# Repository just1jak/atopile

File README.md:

# Atopile Local 0.4.1 source checkpoint

**Moving to another computer? Start with [CONTINUE-HERE.md](CONTINUE-HERE.md).**
It covers this source checkpoint and the unfinished integrated-SD scanner PCB.

A local VS Code continuation of atopile 0.15.9 with native KiCad schematic
export, ChatGPT through Codex or your own AI provider, local component imports,
and net/placement/DRC tools. This is an independent
fork, not an official atopile release.

This checkpoint preserves the 0.4.1 source and subsequent local KiCad 10
editing, Codex tool-catalog, and startup fixes. The installed extension on the
original Mac reports 0.4.1; this newer source checkpoint has not been packaged
as a new release. Its focused backend checks passed **114 tests**. See
[extension-handoff.md](extension-handoff.md) for exact recovery and rebuild steps.

## Start on this Mac

On this Mac, double-click **Open Atopile Local.command** beside the source
folder. It opens the included circuit in VS Code. Select the build target and
choose **Inspect → Schematic**. Other inspection views remain available beside it.

For this checkpoint, rebuild and install from the checked-out source using the
steps in `extension-handoff.md`. An older downloaded release archive installs
that release's source rather than these later changes. The installer registers
the runtime for other VS Code workspaces too. ChatGPT (Codex) is the default AI provider.
Run **Atopile Local: Connect ChatGPT** to reuse your local Codex sign-in or start
Codex's browser sign-in. No separate API key is needed. Your ChatGPT plan's
Codex usage limits apply; this does not grant unlimited usage or add credits.

The connection uses the official local `codex app-server` interface. Codex owns
sign-in, credential storage, and renewal. Atopile Local does not copy account
tokens into its settings or webviews. It requires ChatGPT authentication and
will not silently switch to API billing. The compiler and circuit tools still
run locally; prompts and tool results go to OpenAI for AI assistance.

Use **Atopile Local: Configure AI Provider** to select a separate OpenAI-compatible
or Anthropic provider instead, then **Atopile Local: Set AI API Key** to store that
provider's key in VS Code. Optional `atopileLocal.agent.codexPath` selects a Codex
executable; leave it blank for automatic discovery. A blank model uses Codex's
default model when ChatGPT is selected.

The compiler, parts, and viewers work without AI. API providers require their
own key; a loopback model server may omit a key. OpenAI-compatible
endpoints must implement the Responses API, streaming, and tool calls. Datasheet
file search also requires Files/Vector Stores support. A Chat Completions-only
server is not supported by this release. Leave the endpoint blank for the
selected provider's default; custom Anthropic endpoints use the API origin
rather than an OpenAI-style `/v1` suffix. Your provider's prices/limits apply.

## Portable setup

Requires VS Code 1.105+, uv, and KiCad for native schematic export, layout and DRC. ChatGPT assistance
also requires a Codex CLI with app-server dynamic tools and a ChatGPT plan that
includes Codex access. Tested on Apple
Silicon macOS with Python 3.14.6 and KiCad 10.0.7. The `.command` launcher is
for macOS; Linux can use `python3 local/launch.py`. Windows launcher packaging
is not included.

Keep the engine outside iCloud, OneDrive, and other folders that automatically
offload files. The current fork includes a verified installer that puts it in
local application storage (on macOS, `~/Library/Application Support/Atopile Local`).
Download the release source ZIP, `SHA256SUMS.txt`, and VSIX, then run this from
the fork checkout:

```sh
python3 local/install_local_runtime.py \
  --archive /path/to/atopile-local-source.zip \
  --checksum-file /path/to/SHA256SUMS.txt
python3 local/launch.py
```

Download the source and extension from the
[GitHub release](https://github.com/just1jak/atopile/releases/tag/local-v0.4.0),
or clone the fork's `feature/atopile-local` branch for the installer. Before
launching, install the VSIX using VS Code's **Extensions: Install from VSIX**
command. The installer verifies the archive, installs pinned dependencies,
and checks startup before changing VS Code's runtime location. Failed setup
keeps the previous location; retrying the same archive resumes setup.
To open another existing project, use `python3 local/launch.py /path/to/project`.

```sh
git clone --branch feature/atopile-local https://github.com/just1jak/atopile.git
cd atopile
```

For this source checkpoint, use a fully local checkout, run
`python3 local/setup_runtime.py`, rebuild with `python3 local/build_extension.py`,
then install using `python3 local/install_extension.py`. Do not use `--download`
when you intend to run the checkpoint source and its rebuilt UI.

The native compiler is the pinned atopile 0.15.9 wheel. Modified Python source
runs over that wheel, avoiding a local Zig rebuild. The wrapper uses safe
Python import precedence and stores fork state in `.state/`; it disables atopile
telemetry and migration-notice requests. The runtime handoff goes in this fork's
own VS Code global storage and does not alter official atopile settings.

## Local design workflow

```sh
bin/ato-local build examples/offline-indicator --target default
bin/ato-local create part-from-kicad --help
bin/ato-local create part-from-pinout --help
```

Open the **Atopile Local** activity-bar view to build, browse components and
nets, inspect pinouts, and open the PCB/3D viewers. The independent agent can
edit project files, build and debug circuits, read logical nets, inspect or
change placements (with backups), add or delete copper, and run KiCad DRC.

## Board access in chat

The chat identifies itself as **Atopile Local** and shows its configured AI
provider. Before each message, the host checks the session's selected PCB with
the local inspection tool. **Board last read** reports the checked target,
part count, and net count. A failed check shows the actual error.

The agent can read placement and logical nets, move or rotate unlocked
components, add straight track segments and through-vias, delete copper by
UUID, and run KiCad DRC. Placement changes preserve existing tracks but do not
reroute them. Copper tools require explicit net, canonical copper layer, and
geometry; creating a segment does not prove its clearance or complete routing.
Ask it to inspect the board first, state any fixed connector positions and
board dimensions, and review native DRC after edits.

KiCad 10 edits preserve unsupported source fields and unrelated native locks.
Locked targets and `FBRK:notouch` geometry are protected. The scoped editor
supports placement and copper changes; settings, net membership, zone changes,
new footprints, and complex flips remain native KiCad work. Stale external
changes are rejected instead of overwritten, and successful edits create
backups. Save edits in KiCad before switching editors.

Version 0.3.1 fixes Codex tool discovery for the full production tool catalog.
After updating, reload the VS Code window so the backend and tool bridge restart.
Existing chat history is retained.

## Schematics in KiCad

After building, open **Inspect → Schematic** and choose **Open in KiCad**.
If the project has a native schematic, explicitly map it to the build target
in `.atopile-local.json`:

```json
{"schematics": {"v240": "elec/schematic/ChryslerScanner_V240.kicad_sch"}}
```

Normal opening preserves that file and all child sheets. Paths must remain
inside the selected project; the hierarchy is validated before native KiCad
reads it. The app does not guess which existing schematic belongs to a target.

For projects without a mapping, Atopile Local saves a real `.kicad_sch` file, with embedded KiCad symbols and
nets taken from the PCB's actual pad assignments, then opens KiCad's Schematic
Editor. KiCad must be installed: each new snapshot is checked using its native
netlist exporter. The saved file remains available if the editor cannot launch.

The panel shows the saved file's location. Reopening the same circuit revision
uses the saved file, preserving edits made in KiCad. **Generate new from circuit**
creates a separate snapshot and opens it; it never overwrites an earlier file.
Exports live under the selected target's build output in a `schematic` folder.
Keep a copy outside `build/` before cleaning build artifacts.

This is a code-to-schematic export: edits in KiCad do not update `.ato` source.
The existing PCB is left in place. Source and PCB footprint identifiers are
included as symbol properties, but native KiCad PCB cross-probing/relinking is
not established by this export. Missing symbols, unsupported multi-unit parts,
and ambiguous pin mappings stop export with a specific error. This initial
exporter supports up to 256 components per snapshot.

**Preview connections** opens the optional inline preview with net highlighting
and links to source declarations and the PCB view. Its wiring describes logical
connections rather than physical PCB trace routes. Power/data Trees remain
separate views and may be empty for generic parts.

The routed offline indicator has three local components, three nets, and a
32 x 18 mm outline. Its layout is a specific hand-authored recipe. Generic
local parts are included in the JSON BOM; unsourced parts are excluded from the
JLCPCB assembly CSV. See `examples/offline-indicator/README.md`.

## Service boundaries

Local builds with locally imported parts do not need atopile sign-in. Automatic
online component selection still uses atopile's service and requires sign-in.
DeepPCB automatic placement/routing remains hosted and is labeled in the UI;
no general local autorouter is included. Web search uses your own `EXA_API_KEY`.
Manual local layout and local agent placement/DRC do not use those services.
The KiCad 10 source-preserving adapter retains native locks and rejects edits
to locked targets. Unsupported changes stop with an error rather than dropping
unknown native fields.

## Rebuild and verify

```sh
python3 local/build_extension.py
PYTHONPATH=$PWD/src ATOPILE_LOCAL_DATA_DIR=$PWD/.state FBRK_TELEMETRY=0 \
  .venv/bin/python -m pytest test/agent test/libs/test_kicad_part_import.py \
  test/exporters/pcb/kicad/test_pcb_transformer.py -q
.venv/bin/python local/verify_backend.py
python3 local/verify_offline.py
```

The recovered checkpoint passed 114 focused backend tests, including native
KiCad edit/connectivity checks and mocked Codex protocol checks, on 2026-10-20.
The full frontend dependency install, TypeScript checks, and VSIX rebuild were
not repeated for this checkpoint. See `extension-handoff.md` for the exact test
command and the distinction from older release verification.

The earlier verification record is `local/VERIFICATION.json`; demo connectivity and DRC
reports are under `examples/offline-indicator/`. No physical hardware test was
performed. Passing DRC does not verify electrical behavior or supplier suitability.

## Source and licenses

Based on the public PyPI atopile 0.15.9 source distribution, SHA-256
`681cc1e123646dd133de31b631aedaf4eaac88682613b4f82d1da4b3ef8b4e8e`.
Upstream MIT notices are retained; local import work retains the Axiovel MIT
attribution in `local/IMPORTER_ATTRIBUTION.md`. Bundled 3D decoders include their
Apache-2.0 notices and Three.js MIT license. The original README is preserved
at `local/UPSTREAM_README.md`. The three standard KiCad demo symbols retain
their CC-BY-SA 4.0 library license and exception in
`examples/offline-indicator/assets/KICAD-SYMBOLS-LICENSE.md`.

Codex-managed ChatGPT authentication is documented for local/open-source apps.
This integration is for local use; a hosted or commercial service needs its own
supported sign-in integration. See [OpenAI's app-server documentation](https://learn.chatgpt.com/docs/app-server).

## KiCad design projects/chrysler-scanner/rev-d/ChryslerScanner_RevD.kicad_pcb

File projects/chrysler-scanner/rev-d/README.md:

# Rev D switchable legacy and CAN diagnostics

Open [ChryslerScanner_RevD.kicad_pro](ChryslerScanner_RevD.kicad_pro) in KiCad
10. Sheet 25 is the CAN transceiver, sheet 26 switches OBD pins 6 and 14
between CAN and the retained legacy branches, and sheet 27 gates CAN TX.
Sheet 28 adds series isolation and a hardware transmit timer. This is a
development revision. Use the board and schematic from the same revision.

## Mode control

U26 is an MCP23008 on the existing I2C bus at seven-bit address 0x20. GP0
requests CAN and GP1 requests Legacy. Both request lines have pull-downs.
U27 decodes the requests in hardware and its enable is driven by N_R88_2,
the existing supervised expander reset/permit. That net also resets U26
and cuts the coil return through Q27. Only the normally open contacts of
K1 and K2 are wired to the bus branches. K3 is in series with K1 and K4
is in series with K2. K3 and K4 have separate coil sinks driven by the
raw decoder outputs and the hardware permit. The primary relays use
delayed decoder outputs. A closed contact or a stuck-on coil driver in
one relay leaves the other contact in series on each conductor able to
isolate the unselected branch.

| Hardware permit | Request GP1:GP0 | OBD pins 6 and 14 |
| --- | --- | --- |
| Low | Any | Both branches open after relay release |
| High | 00 | Both branches open |
| High | 01 | CAN branch only |
| High | 10 | Legacy branch only |
| High | 11 | Both branches open |

The 110 × 96 mm PCB extends the lower edge by 41 mm from Rev C to make
room for the selector, series relays and TX interlock. It retains the
four Rev C mounting-hole centers.
Confirm the revised outline and enclosure fit before releasing fabrication.

Each relay has a delayed pickup and quicker turnoff path from the decoder
through its RC network and Schmitt buffer. The firmware must write 00
between modes and wait through the qualified contact release, bounce and
discharge interval before requesting the other mode. Firmware startup
must clear the output latch before configuring the request GPIOs as outputs.
Drop the hardware permit if expander setup, readback or a mode transition
fails. CCD, PCI and SCI receive on pins 7/15 retain their existing wiring.

CAN RXD feeds GPIO39. STB defaults high and is pulled low for CAN capture.
D40 protects the CAN branch. The selector restores physical access to the
legacy branches. Existing firmware continues to inhibit VBB/VPP and active
transmission. A future programming release requires independent isolation
and contact-state safeguards. A coil command or expander readback cannot
prove that a contact opened.

## Active diagnostics and passive default

U26 GP2 is the TX arm request and defaults low through R146. U29 through
U31 require the hardware permit, the raw CAN decode, the delayed CAN relay
command, a low Legacy relay command and the explicit arm. U32 is a buffer
with a high impedance output when the permit is low. R149 then holds the
transceiver TXD high, which is the recessive state. The raw decode disables
TX when leaving CAN even if the delayed CAN relay signal is still high.
U33 is a rising-edge, nonretriggerable LTC6993-1 with a nominal 1.028 s
window. U34 requires both the window and the original arm. Dropping the
arm cancels TX immediately, and an arm held high cannot extend the pulse.
The firmware's 900 ms window still governs normal requests. A later arm
edge can start another hardware window after the one-shot has rearmed.
On reset, the selector opens both branches. Selecting CAN with GP2 low
gives the passive capture mode and permits TWAI to run in listen-only mode.

U10 GPIO2, pad 22, is the Rev D TWAI TX candidate and connects only to the
buffer input and a 47 kΩ pull-down. This keeps the required low strap for
joint download mode. Verify cold boot and USB download across supplies and
temperatures. Firmware must establish recessive TX before asserting GP2.

Build the firmware with `pio run -e rev_d_can` from the firmware directory.
Use the USB CLI on a terminated bench bus once the board is qualified.

```powershell
python tools/scanner.py can-mode passive --port COM7 --bitrate 500000
python tools/scanner.py can-read pid --port COM7 --pid 0x0c
python tools/scanner.py can-read dtc --port COM7
python tools/scanner.py can-read vin --port COM7
python tools/scanner.py can-mode legacy --port COM7
python tools/scanner.py can-mode open --port COM7
```

The selector starts open. Selecting CAN starts TWAI in listen-only mode.
An explicit USB lease and request are required to arm TX. The diagnostic
window has a 900 ms software budget and returns to listen-only after a reply
or timeout. A controller or ISO-TP fault drops the arm and opens the selector.
The CH340 provides no physical USB disconnect signal to the MCU.
Active mode can send requests, ISO-TP flow control, ACKs, and error frames.
The implementation supports 250/500 kbit/s Classical CAN with standard IDs,
functional read-only OBD requests, and one ISO-TP responder per request.
Desktop and mobile diagnostic controls are outside this firmware target.
Relay timing and isolation still require physical verification.

## Checks and bring-up

KiCad 10 full DRC reports zero violations, unconnected items or schematic
parity issues. The pad connectivity audit finds all 246 ground pads in one
group. The MCU fanout uses a local CAN RX escape on L2. Keep the
filled-and-capped processing specified in the board for vias whose drills
intersect SMD lands.

KiCad 10 all-severity ERC passed with zero violations. The netlist checker
compares every net to Rev C plus the declared changes and evaluates all eight
steady-state permit/request combinations using the normally open relay contacts.
The TX logic check covers 128 combinations of route request, hardware
permit, relay commands, TX arm and the timer output. Only the fully
enabled CAN state allows TX. The contact model
forces each relay closed in turn and checks isolation on both conductors.
It covers one stuck relay or driver. The decoder, supply and supervisor
remain common to the drive paths. Bench checks cover physical timing
and leakage.

```powershell
kicad-cli sch erc --severity-all --exit-code-violations ChryslerScanner_RevD.kicad_sch
kicad-cli sch export netlist --format kicadxml -o rev-d-netlist.xml ChryslerScanner_RevD.kicad_sch
python check_netlist.py rev-d-netlist.xml
kicad-cli pcb drc --all-track-errors --schematic-parity --severity-all --refill-zones --exit-code-violations ChryslerScanner_RevD.kicad_pcb
```

Before fabrication release, verify mechanical land patterns and the relay supply
and permit loading. Measure the minimum pickup delay and maximum release and
bounce including diode flyback, tolerance, temperature, supply sequencing
and rapid changes. Check both poles during MCU reset, missing heartbeat,
brownout and recovery. Short one normally open contact or force one coil
driver on at a time and verify that the other series contact isolates the
unselected branch. Qualify these cases
before connecting a vehicle or permitting programming voltages. Confirm
CAN signal quality and listen-only capture on a terminated bench bus
with separate transmitting and acknowledging nodes.

Exercise PID, DTC and multi-frame VIN responses on the bench at both bit
rates. Scope TXD and both relay outputs during the request, response, timeout
and bus-off cases. Confirm passive capture contributes no ACK, verify
transmit permit removal on lease release, and measure the time to recessive
TXD after a watchdog fault. With CAN selected and the heartbeat running,
hold the arm high through expiry and scope the timer output, buffer enable
and TXD. Repeat with an arm drop during the pulse and with trigger edges
during the pulse to verify immediate cancel and no pulse extension.

[Relay datasheet](https://components.omron.com/sites/default/files/datasheet_pdf/K106-E1.pdf)
· [I2C expander datasheet](https://ww1.microchip.com/downloads/en/DeviceDoc/MCP23008-MCP23S08-Data-Sheet-20001919F.pdf)
· [CAN transceiver datasheet](https://www.ti.com/lit/ds/symlink/tcan1042h-q1.pdf)

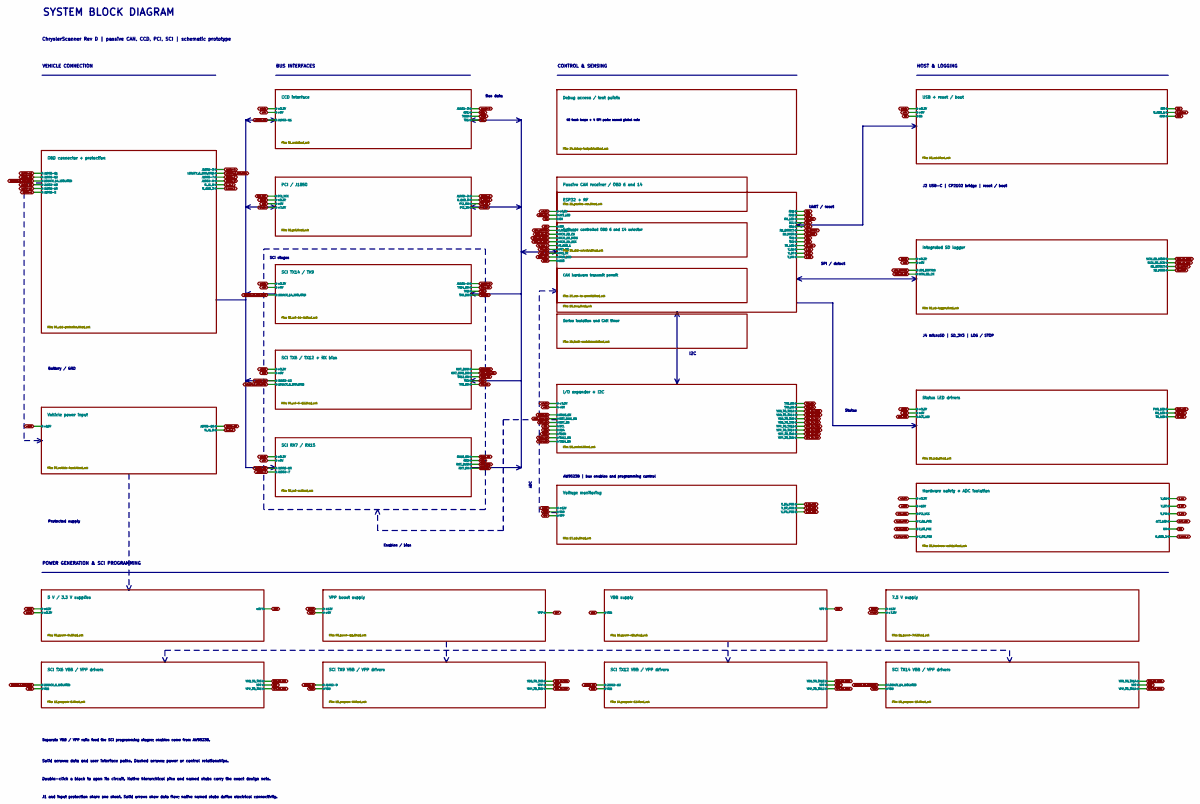
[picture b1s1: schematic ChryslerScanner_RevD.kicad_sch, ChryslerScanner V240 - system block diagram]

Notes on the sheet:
SYSTEM BLOCK DIAGRAM
ChryslerScanner Rev D | passive CAN, CCD, PCI, SCI | schematic prototype
VEHICLE CONNECTION
BUS INTERFACES
CONTROL & SENSING
HOST & LOGGING
SCI stages
Bus data
UART / reset
SPI / detect
Status
I2C
ADC
Enables / bias
Battery / GND
Protected supply
POWER GENERATION & SCI PROGRAMMING
Separate VBB / VPP rails feed the SCI programming stages; enables come from AW9523B.
J2 USB-C | CP2102 bridge | reset / boot
J4 microSD | SD_3V3 | LOG / STOP
AW9523B | bus enables and programming control
Solid arrows: data and user interface paths. Dashed arrows: power or control relationships.
Double-click a block to open its circuit. Native hierarchical pins and named stubs carry the exact design nets.
J1 and input protection share one sheet. Solid arrows show data flow; native named stubs define electrical connectivity.
48 hook loops + 4 SPI pads; named global nets

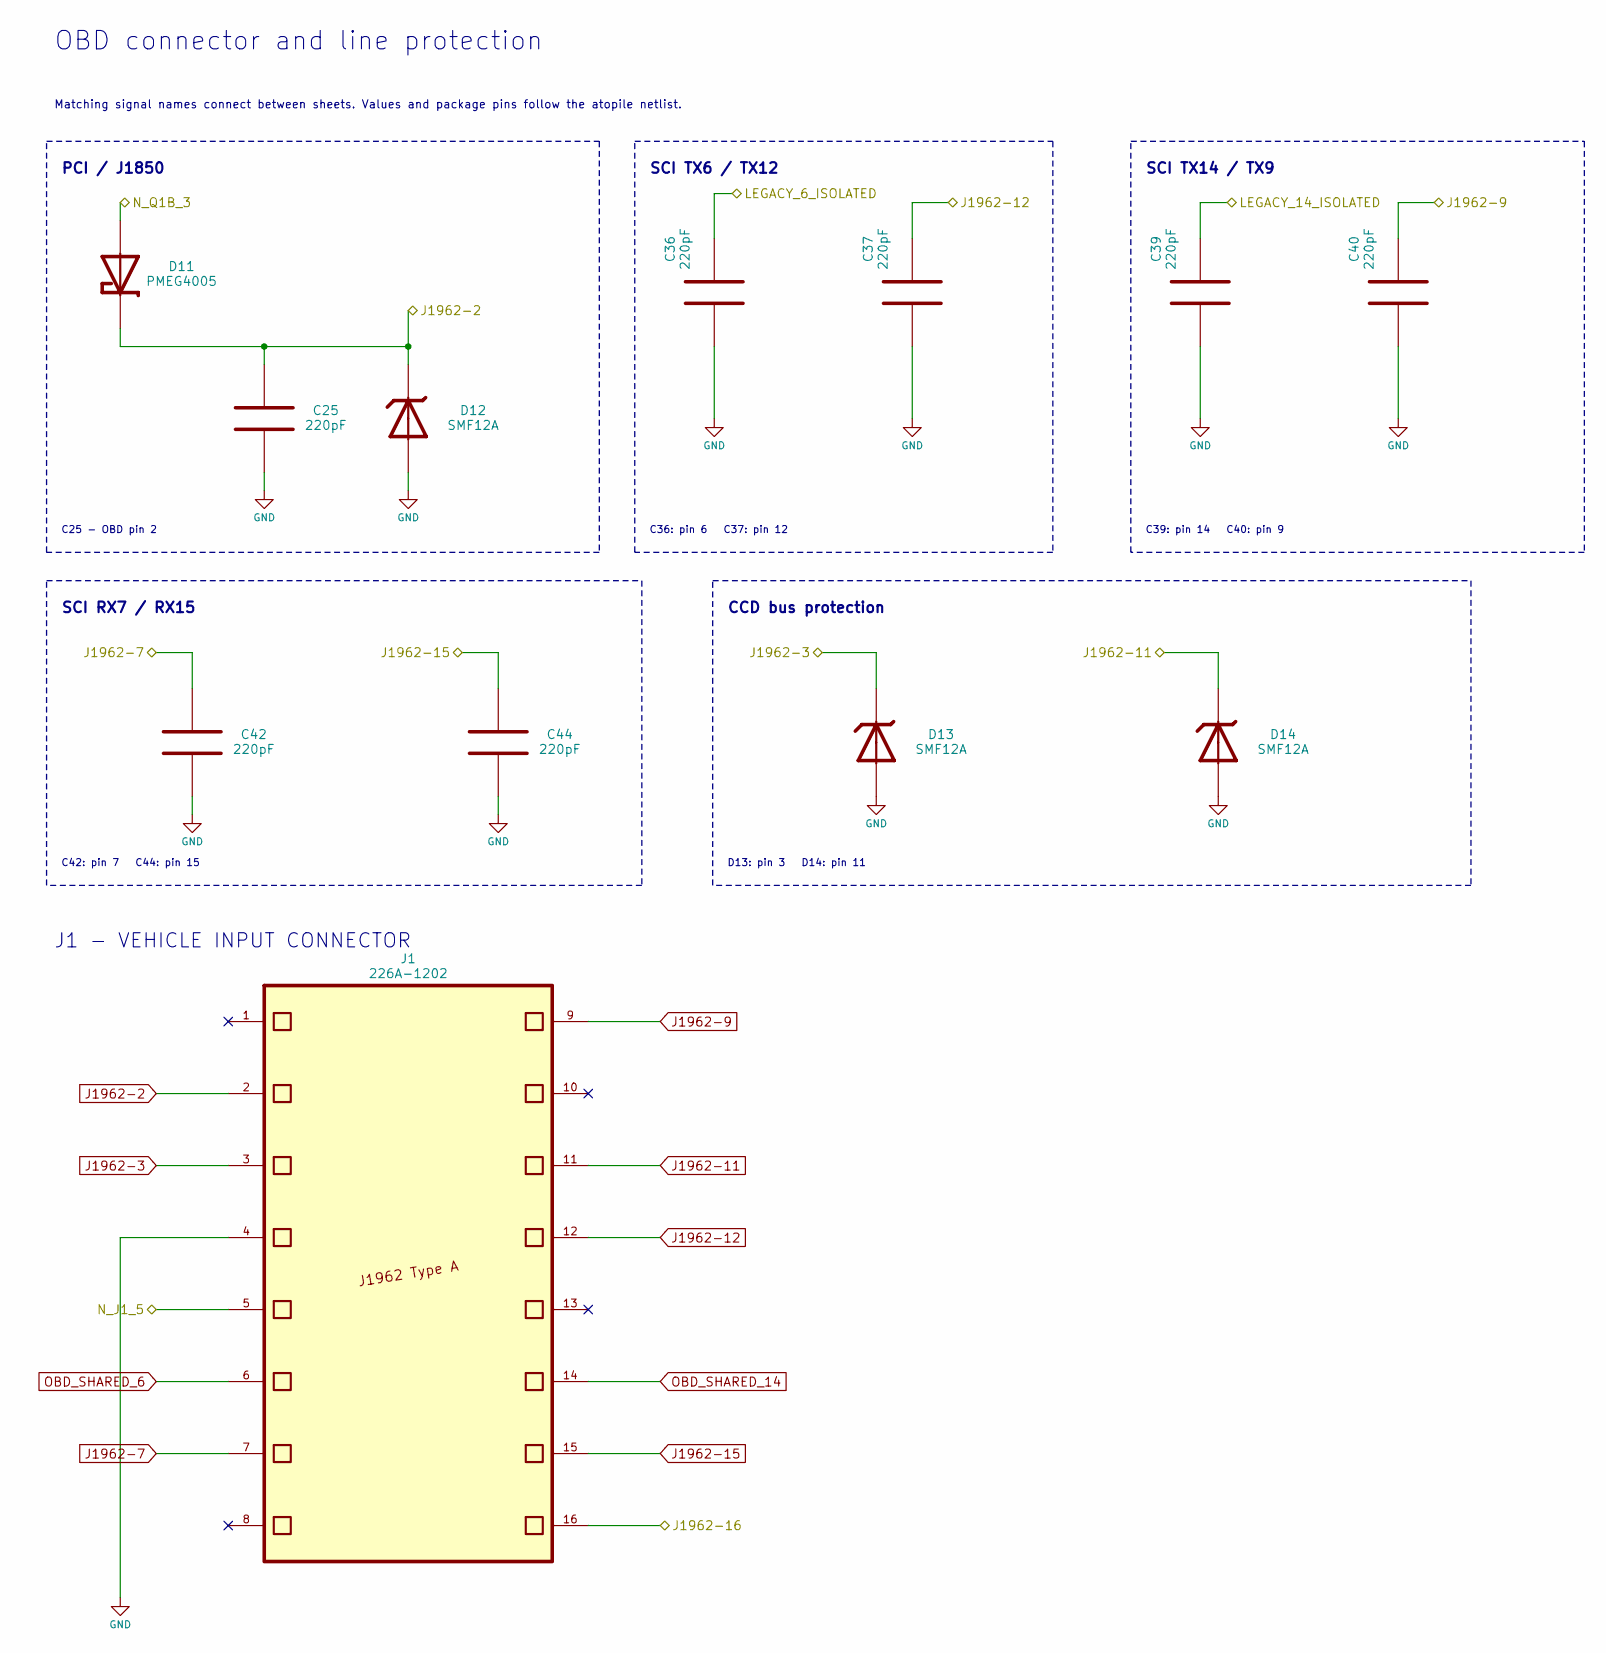
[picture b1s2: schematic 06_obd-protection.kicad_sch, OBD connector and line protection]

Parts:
C25, C36, C37, C39, C40, C42, C44: 220pF; C_0603_1608Metric; Selected Voltage Rating 100V; Tolerance 5%; MPN C0603C221J1GACTU
D11: PMEG4005; D_SOD-123; MPN PMEG4005EGWX
D12, D13, D14: SMF12A; D_SOD-123; MPN SMF12A
J1: 226A-1202; OBDII_ATTEND_226A-1202; MPN 226A-1202

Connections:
GND: C25.2, C36.1, C37.1, C39.1, C40.1, C42.2, C44.2, D12.2, D13.2, D14.2, J1.4; also elsewhere on the board
J1962-2: C25.1, D11.1, D12.1, J1.2; also elsewhere on the board
J1962-3: D13.1, J1.3; also elsewhere on the board
J1962-7: C42.1, J1.7; also elsewhere on the board
J1962-9: C40.2, J1.9; also elsewhere on the board
J1962-11: D14.1, J1.11; also elsewhere on the board
J1962-12: C37.2, J1.12; also elsewhere on the board
J1962-15: C44.1, J1.15; also elsewhere on the board
J1962-16: J1.16; also elsewhere on the board
LEGACY_6_ISOLATED: C36.2; also elsewhere on the board
LEGACY_14_ISOLATED: C39.2; also elsewhere on the board
N_J1_5: J1.5; also elsewhere on the board
N_Q1B_3: D11.2; also elsewhere on the board
OBD_SHARED_6: J1.6; also elsewhere on the board
OBD_SHARED_14: J1.14; also elsewhere on the board

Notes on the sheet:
J1 - VEHICLE INPUT CONNECTOR
Matching signal names connect between sheets. Values and package pins follow the atopile netlist.
OBD connector and line protection
PCI / J1850
C25 - OBD pin 2
SCI TX6 / TX12
C36: pin 6 C37: pin 12
SCI TX14 / TX9
C39: pin 14 C40: pin 9
SCI RX7 / RX15
C42: pin 7 C44: pin 15
CCD bus protection
D13: pin 3 D14: pin 11

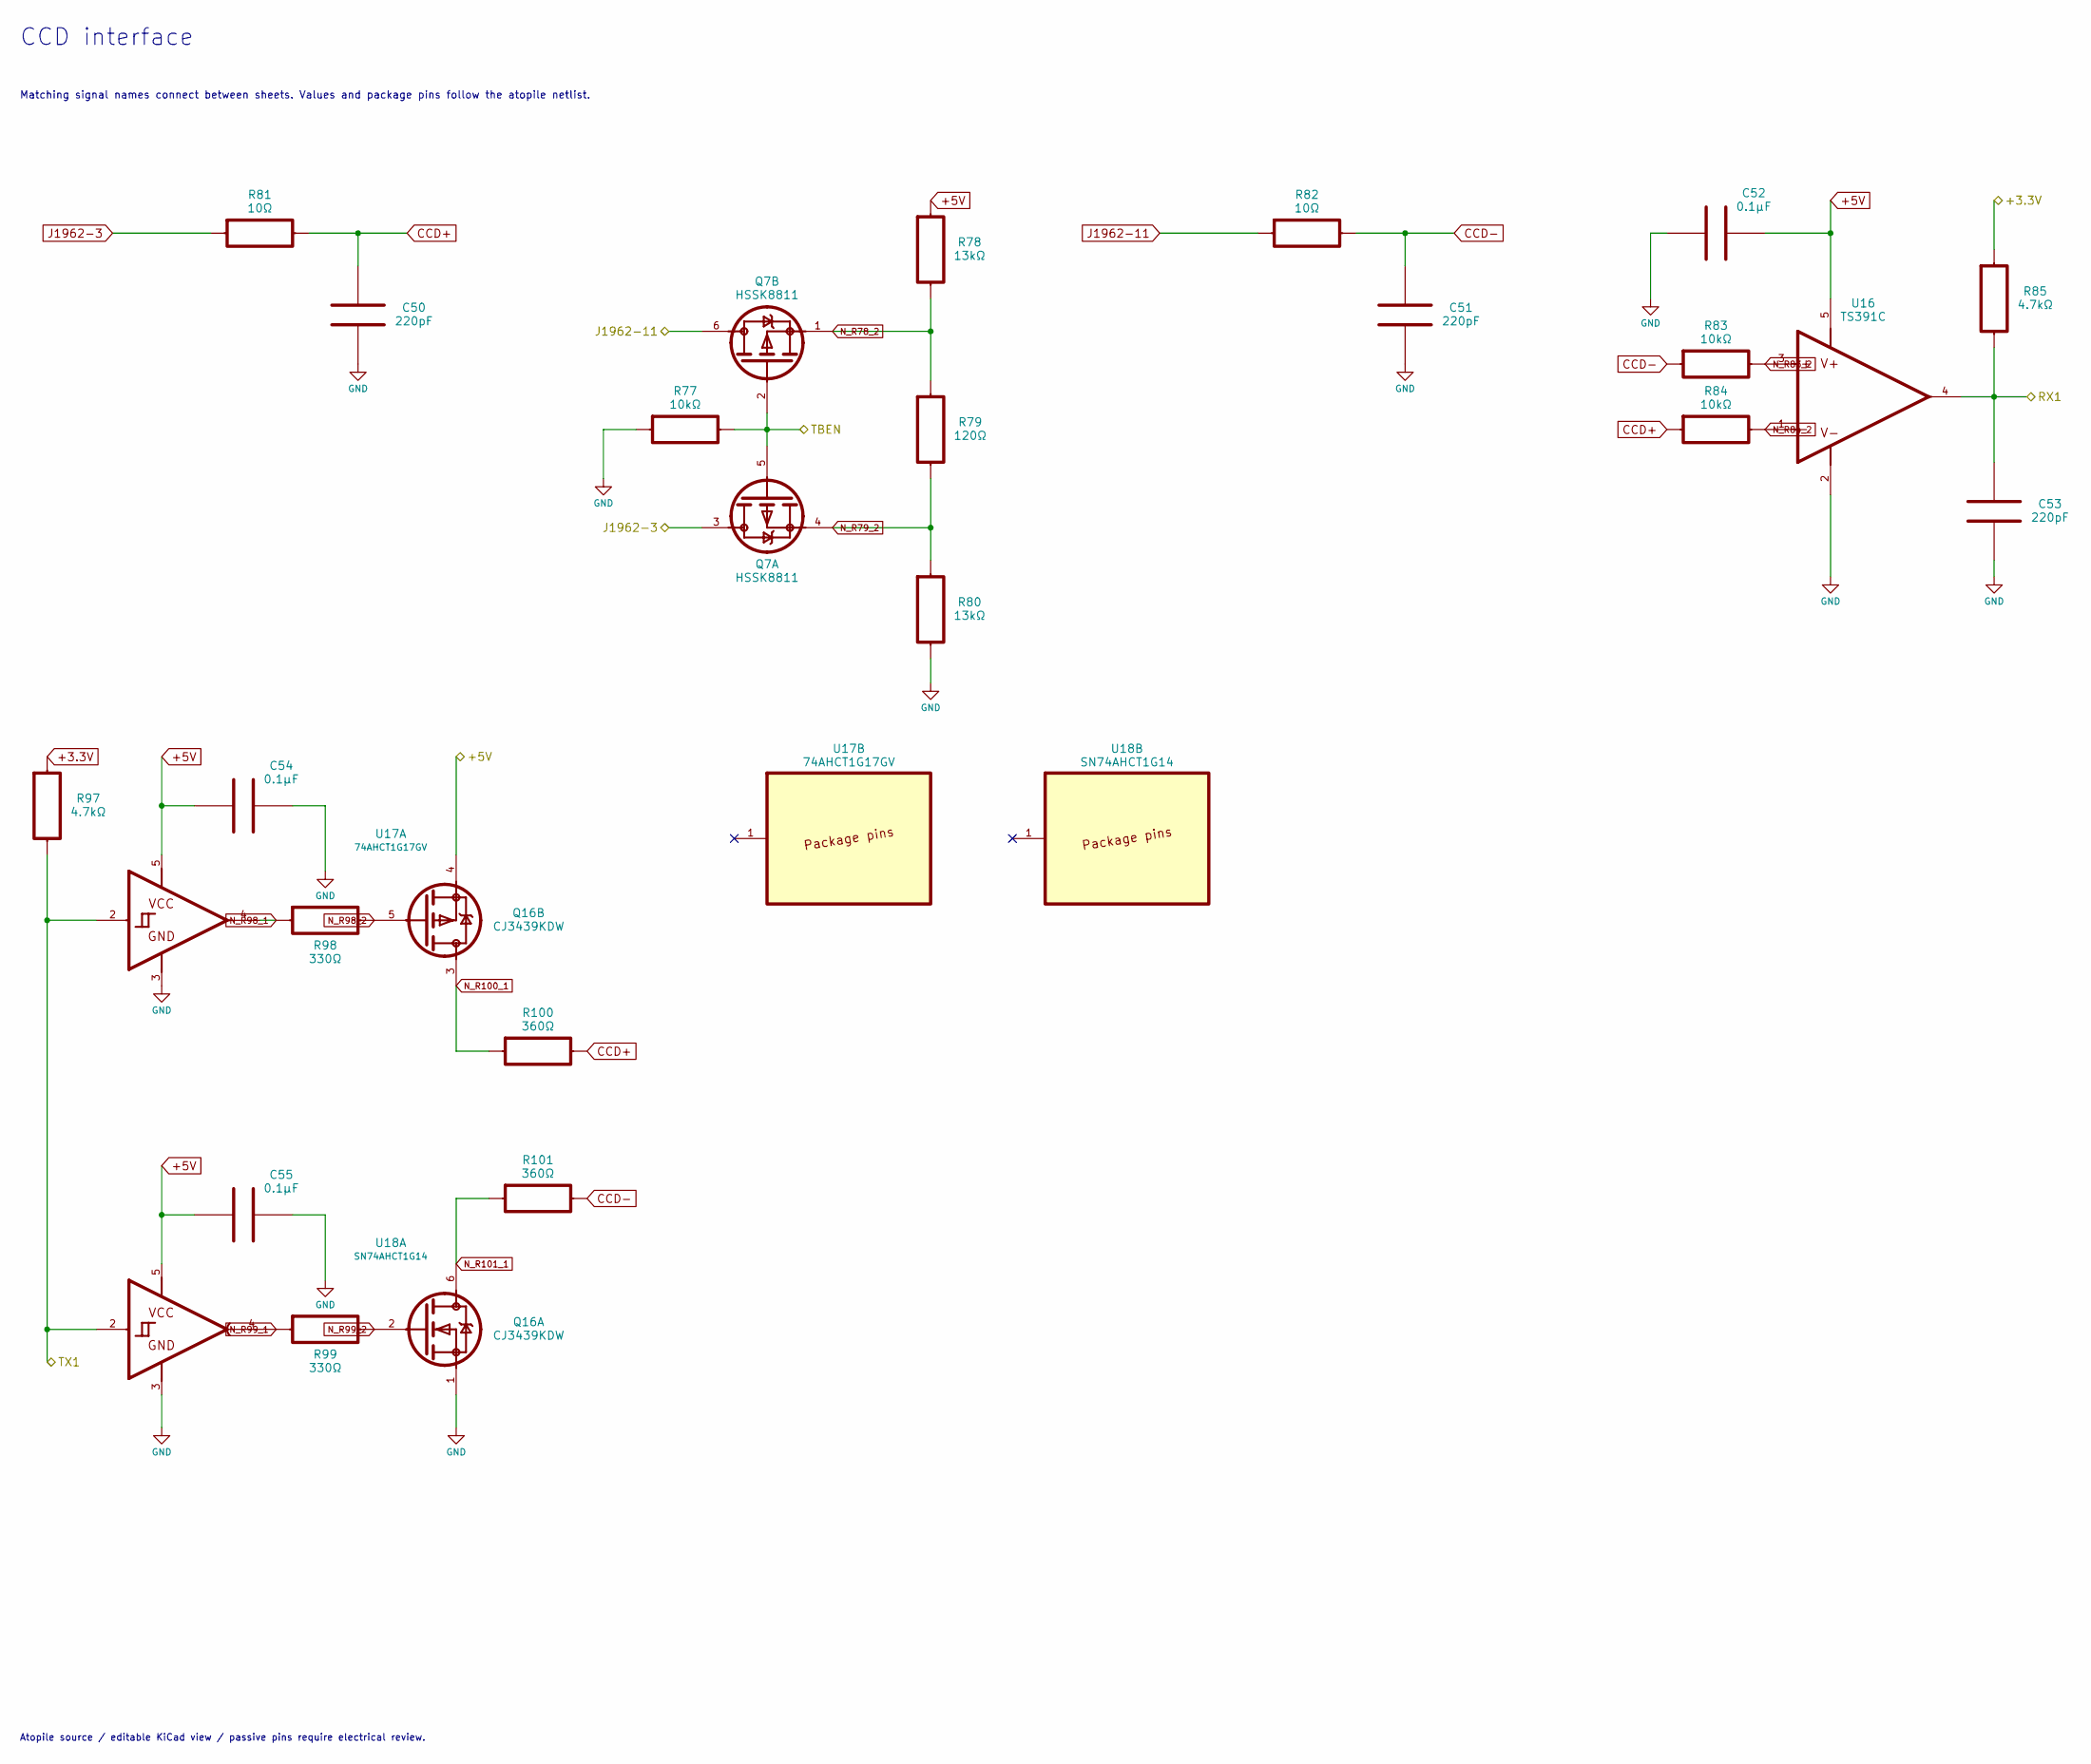
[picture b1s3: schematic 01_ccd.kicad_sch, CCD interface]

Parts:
C50, C51, C53: 220pF; C_0603_1608Metric; Selected Voltage Rating 100V; Tolerance 5%; MPN C0603C221J1GACTU
C52, C54, C55: 0.1μF; C_0603_1608Metric; Selected Voltage Rating 50V; Tolerance 10%; MPN C0603C104K5RACTU
Q7: HSSK8811; SOT-363_SC-70-6_RR; MPN HSSK8811
Q16: CJ3439KDW; SOT-363_SC-70-6_RR; MPN CJ3439KDW
R77, R83, R84: 10kΩ; R_0603_1608Metric; Tolerance 1%; MPN CRCW060310K0FKEA
R78, R80: 13kΩ; R_0603_1608Metric; Tolerance 1%; MPN CRCW060313K0FKEA
R79: 120Ω; R_0603_1608Metric; Tolerance 1%; MPN CRCW0603120RFKEA
R81, R82: 10Ω; R_0603_1608Metric; Tolerance 1%; MPN CRCW060310R0FKEA
R85, R97: 4.7kΩ; R_0603_1608Metric; Tolerance 1%; MPN CRCW06034K70FKEA
R98, R99: 330Ω; R_0603_1608Metric; Tolerance 1%; MPN CRCW0603330RFKEA
R100, R101: 360Ω; R_0603_1608Metric; Tolerance 1%; MPN CRCW0603360RFKEA
U16: TS391C; SOT-23-5; MPN TS391ILT
U17: 74AHCT1G17GV; SOT-23-5; MPN 74AHCT1G17GVH
U18: SN74AHCT1G14; SOT-23-5; MPN SN74AHCT1G14DBVR

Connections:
+3.3V: R85.1, R97.1; also elsewhere on the board
+5V: C52.2, C54.1, C55.1, Q16.4, R78.1, U16.5, U17.5, U18.5; also elsewhere on the board
CCD+: C50.1, R81.2, R84.1, R100.2; also elsewhere on the board
CCD-: C51.1, R82.2, R83.1, R101.2; also elsewhere on the board
GND: C50.2, C51.2, C52.1, C53.2, C54.2, C55.2, Q16.1, R77.1, R80.2, U16.2, U17.3, U18.3; also elsewhere on the board
J1962-3: Q7.3, R81.1; also elsewhere on the board
J1962-11: Q7.6, R82.1; also elsewhere on the board
N_R78_2: Q7.1, R78.2, R79.1
N_R79_2: Q7.4, R79.2, R80.1
N_R83_2: R83.2, U16.3
N_R84_2: R84.2, U16.1
N_R98_1: R98.1, U17.4
N_R98_2: Q16.5, R98.2
N_R99_1: R99.1, U18.4
N_R99_2: Q16.2, R99.2
N_R100_1: Q16.3, R100.1
N_R101_1: Q16.6, R101.1
RX1: C53.1, R85.2, U16.4; also elsewhere on the board
TBEN: Q7.2, Q7.5, R77.2; also elsewhere on the board
TX1: R97.2, U17.2, U18.2; also elsewhere on the board

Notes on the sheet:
Atopile source / editable KiCad view / passive pins require electrical review.
Matching signal names connect between sheets. Values and package pins follow the atopile netlist.
CCD interface
